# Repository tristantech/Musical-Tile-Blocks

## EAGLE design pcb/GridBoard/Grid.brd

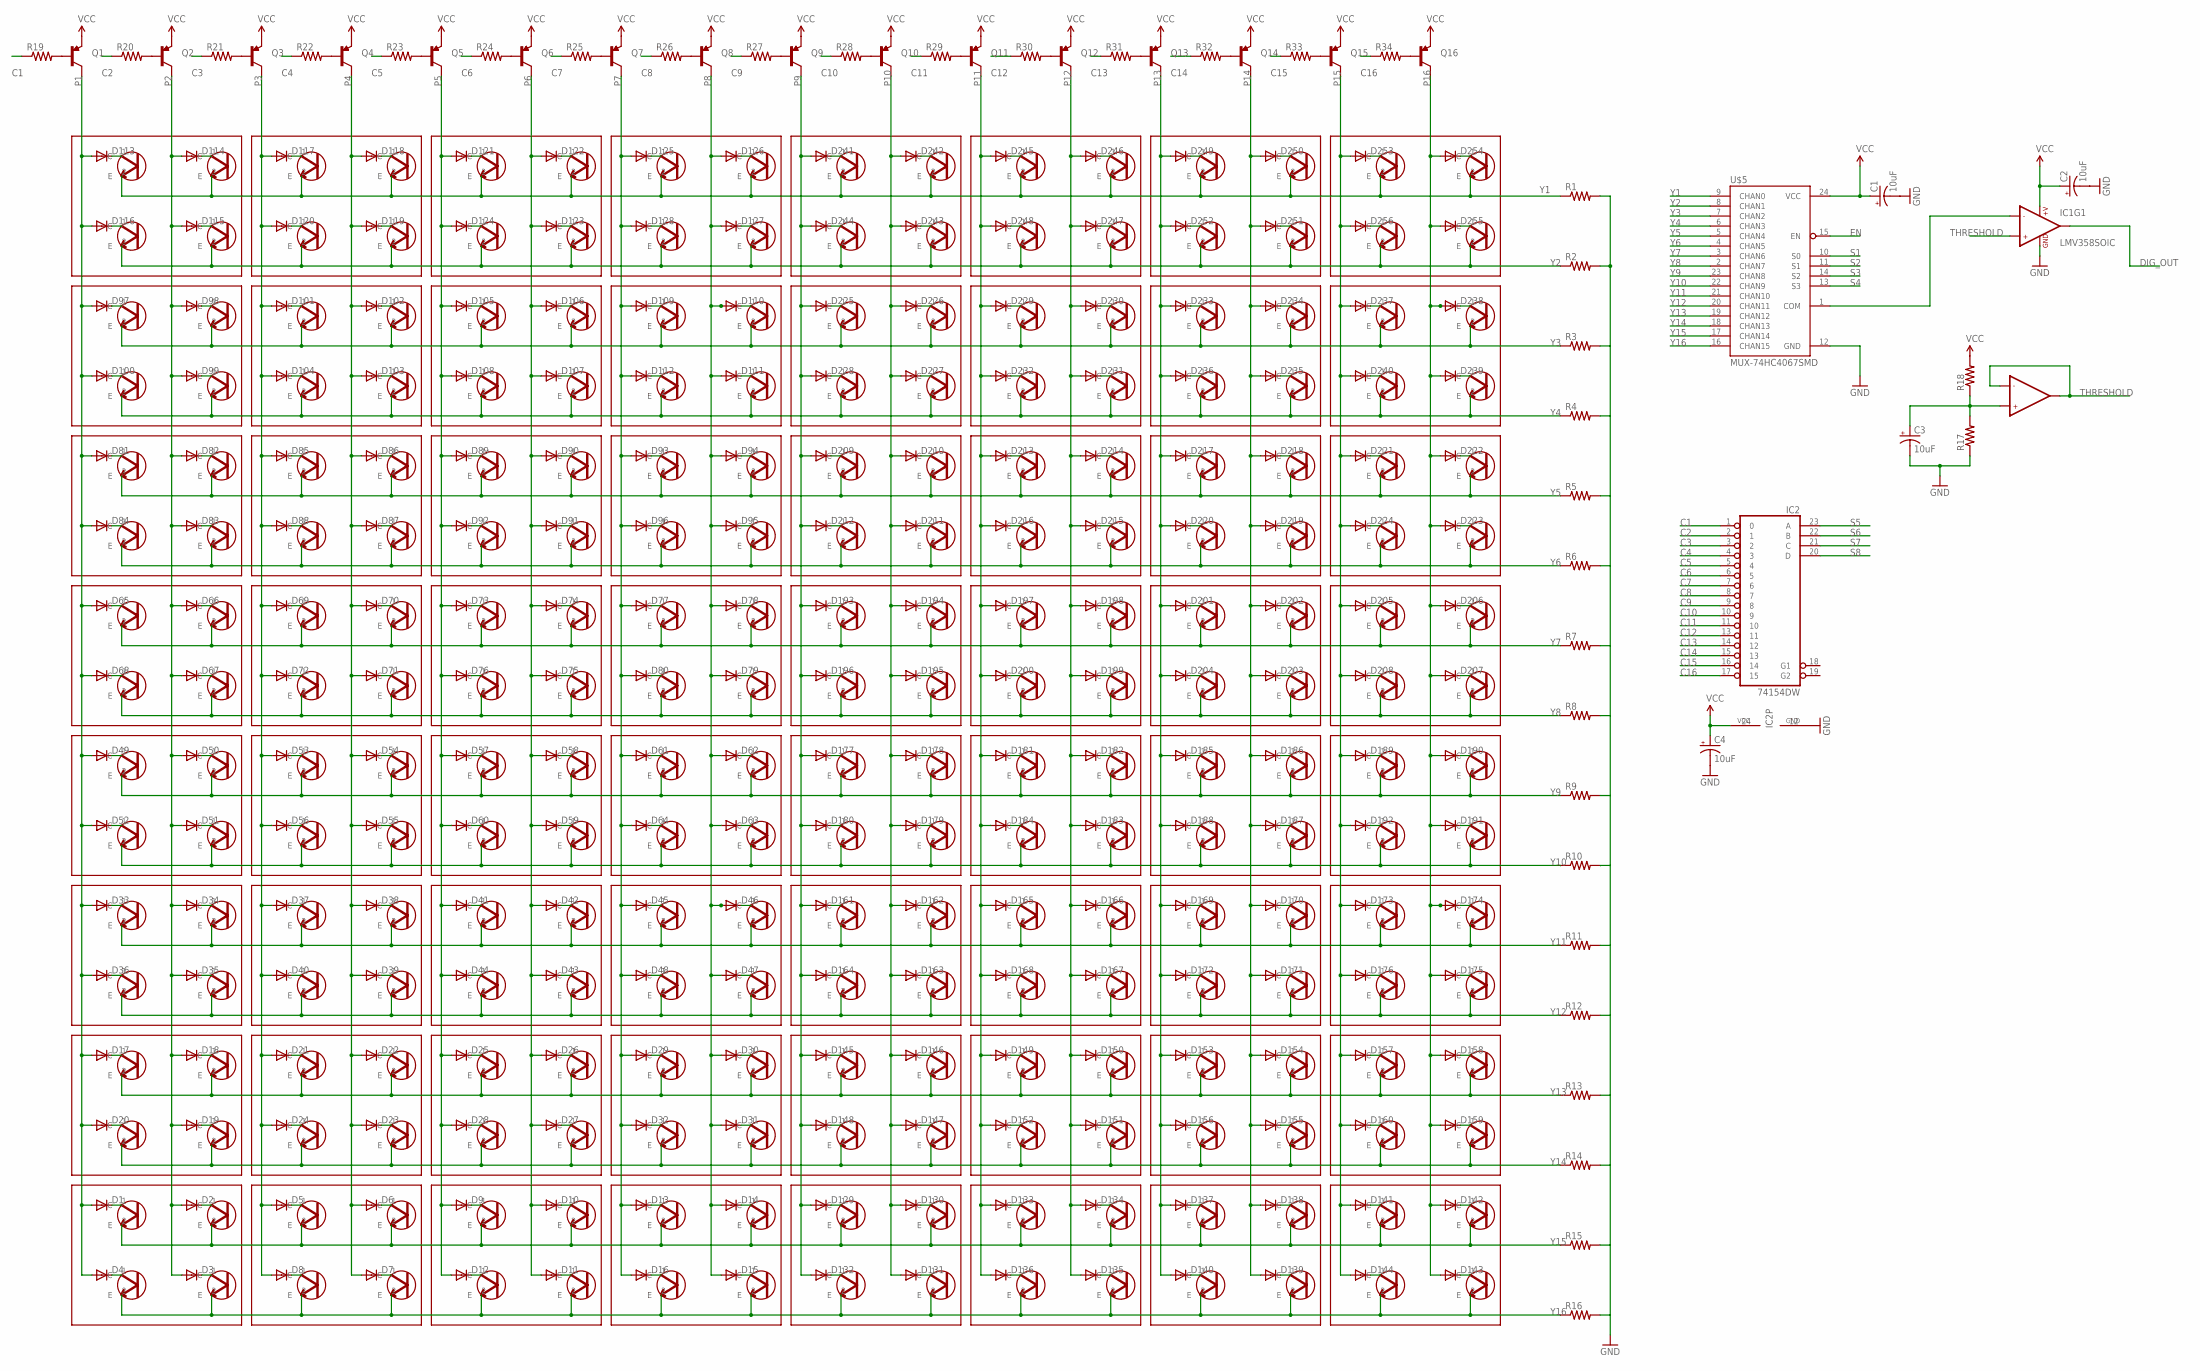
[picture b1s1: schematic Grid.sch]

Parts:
C1, C2, C3, C4: 10uF; EIA3216
D1, D2, D3, D4, D5, D6, D7, D8, D9, D10, D11, D12, D13, D14, D15, D16, D17, D18, D19, D20, D21, D22, D23, D24, D25, D26, D27, D28, D29, D30, D31, D32, D33, D34, D35, D36, D37, D38, D39, D40, D41, D42, D43, D44, D45, D46, D47, D48, D49, D50, D51, D52, D53, D54, D55, D56, D57, D58, D59, D60, D61, D62, D63, D64, D65, D66, D67, D68, D69, D70, D71, D72, D73, D74, D75, D76, D77, D78, D79, D80, D81, D82, D83, D84, D85, D86, D87, D88, D89, D90, D91, D92, D93, D94, D95, D96, D97, D98, D99, D100, D101, D102, D103, D104, D105, D106, D107, D108, D109, D110, D111, D112, D113, D114, D115, D116, D117, D118, D119, D120, D121, D122, D123, D124, D125, D126, D127, D128, D129, D130, D131, D132, D133, D134, D135, D136, D137, D138, D139, D140, D141, D142, D143, D144, D145, D146, D147, D148, D149, D150, D151, D152, D153, D154, D155, D156, D157, D158, D159, D160, D161, D162, D163, D164, D165, D166, D167, D168, D169, D170, D171, D172, D173, D174, D175, D176, D177, D178, D179, D180, D181, D182, D183, D184, D185, D186, D187, D188, D189, D190, D191, D192, D193, D194, D195, D196, D197, D198, D199, D200, D201, D202, D203, D204, D205, D206, D207, D208, D209, D210, D211, D212, D213, D214, D215, D216, D217, D218, D219, D220, D221, D222, D223, D224, D225, D226, D227, D228, D229, D230, D231, D232, D233, D234, D235, D236, D237, D238, D239, D240, D241, D242, D243, D244, D245, D246, D247, D248, D249, D250, D251, D252, D253, D254, D255, D256: DIODESOD; SOD-323
IC1: LMV358SOIC; SO08
IC2: 74154DW; SO24W
Q1, Q2, Q3, Q4, Q5, Q6, Q7, Q8, Q9, Q10, Q11, Q12, Q13, Q14, Q15, Q16: TRANSISTOR_PNPSMD; SOT23-3
R1, R2, R3, R4, R5, R6, R7, R8, R9, R10, R11, R12, R13, R14, R15, R16, R17, R18, R19, R20, R21, R22, R23, R24, R25, R26, R27, R28, R29, R30, R31, R32, R33, R34: RESISTOR0603; 0603-RES
U$1, U$2, U$3, U$4, U$6, U$7, U$8, U$9, U$10, U$11, U$12, U$13, U$14, U$15, U$16, U$17, U$18, U$19, U$20, U$21, U$22, U$23, U$24, U$25, U$26, U$27, U$28, U$29, U$30, U$31, U$32, U$33, U$34, U$35, U$36, U$37, U$38, U$39, U$40, U$41, U$42, U$43, U$44, U$45, U$46, U$47, U$48, U$49, U$50, U$51, U$52, U$53, U$54, U$55, U$56, U$57, U$58, U$59, U$60, U$61, U$62, U$63, U$64, U$65, U$66, U$67, U$68, U$69, U$70, U$71, U$72, U$73, U$74, U$75, U$76, U$77, U$78, U$79, U$80, U$81, U$82, U$83, U$84, U$85, U$86, U$87, U$88, U$89, U$90, U$91, U$92, U$93, U$94, U$95, U$96, U$97, U$98, U$99, U$100, U$101, U$102, U$103, U$104, U$105, U$106, U$107, U$108, U$109, U$110, U$111, U$112, U$113, U$114, U$115, U$116, U$117, U$118, U$119, U$120, U$121, U$122, U$123, U$124, U$125, U$126, U$127, U$128, U$129, U$130, U$131, U$132, U$133, U$134, U$135, U$136, U$137, U$138, U$139, U$140, U$141, U$142, U$143, U$144, U$145, U$146, U$147, U$148, U$149, U$150, U$151, U$152, U$153, U$154, U$155, U$156, U$157, U$158, U$159, U$160, U$161, U$162, U$163, U$164, U$165, U$166, U$167, U$168, U$169, U$170, U$171, U$172, U$173, U$174, U$175, U$176, U$177, U$178, U$179, U$180, U$181, U$182, U$183, U$184, U$185, U$186, U$187, U$188, U$189, U$190, U$191, U$192, U$193, U$194, U$195, U$196, U$197, U$198, U$199, U$200, U$201, U$202, U$203, U$204, U$205, U$206, U$207, U$208, U$209, U$210, U$211, U$212, U$213, U$214, U$215, U$216, U$217, U$218, U$219, U$220, U$221, U$222, U$223, U$224, U$225, U$226, U$227, U$228, U$229, U$230, U$231, U$232, U$233, U$234, U$235, U$236, U$237, U$238, U$239, U$240, U$241, U$242, U$243, U$244, U$245, U$246, U$247, U$248, U$249, U$250, U$251, U$252, U$253, U$254, U$255, U$256, U$257: PT15-21B; 1206
U$5: MUX-74HC4067SMD; SSOP24

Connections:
C1: IC2.1 (0), R19.1
C2: IC2.2 (1), R20.1
C3: IC2.3 (2), R21.1
C4: IC2.4 (3), R22.1
C5: IC2.5 (4), R23.1
C6: IC2.6 (5), R24.1
C7: IC2.7 (6), R25.1
C8: IC2.8 (7), R26.1
C9: IC2.9 (8), R27.1
C10: IC2.10 (9), R28.1
C11: IC2.11 (10), R29.1
C12: IC2.13 (11), R30.1
C13: IC2.14 (12), R31.1
C14: IC2.15 (13), R32.1
C15: IC2.16 (14), R33.1
C16: IC2.17 (15), R34.1
DIG_OUT: IC1.1 (OUT1)
EN: U$5.15 (EN)
GND: C1.C (-), C2.C (-), C3.C (-), C4.C (-), IC1.4 (GND), IC2.12 (GND), R1.2, R2.2, R3.2, R4.2, R5.2, R6.2, R7.2, R8.2, R9.2, R10.2, R11.2, R12.2, R13.2, R14.2, R15.2, R16.2, R17.1, U$5.12 (GND)
unnamed: Q1.1 (B), R19.2
unnamed: Q2.1 (B), R20.2
unnamed: IC1.2 (-IN1), U$5.1 (COM)
unnamed: D2.1 (C), U$2.1 (C)
unnamed: C3.A (+), IC1.5 (+IN2), R17.2, R18.1
unnamed: D1.1 (C), U$1.1 (C)
unnamed: D4.1 (C), U$4.1 (C)
unnamed: D3.1 (C), U$3.1 (C)
unnamed: Q3.1 (B), R21.2
unnamed: Q4.1 (B), R22.2
unnamed: Q5.1 (B), R23.2
unnamed: Q6.1 (B), R24.2
unnamed: D5.1 (C), U$6.1 (C)
unnamed: D6.1 (C), U$7.1 (C)
unnamed: D8.1 (C), U$9.1 (C)
unnamed: D7.1 (C), U$8.1 (C)
unnamed: Q7.1 (B), R25.2
unnamed: Q8.1 (B), R26.2
unnamed: Q9.1 (B), R27.2
unnamed: Q10.1 (B), R28.2
unnamed: D9.1 (C), U$10.1 (C)
unnamed: D10.1 (C), U$11.1 (C)
unnamed: D12.1 (C), U$13.1 (C)
unnamed: D11.1 (C), U$12.1 (C)
unnamed: Q11.1 (B), R29.2
unnamed: Q12.1 (B), R30.2
unnamed: Q13.1 (B), R31.2
unnamed: Q14.1 (B), R32.2
unnamed: D13.1 (C), U$14.1 (C)
unnamed: D14.1 (C), U$15.1 (C)
unnamed: D16.1 (C), U$17.1 (C)
unnamed: D15.1 (C), U$16.1 (C)
unnamed: Q15.1 (B), R33.2
unnamed: Q16.1 (B), R34.2
unnamed: D17.1 (C), U$18.1 (C)
unnamed: D18.1 (C), U$19.1 (C)
unnamed: D20.1 (C), U$21.1 (C)
unnamed: D19.1 (C), U$20.1 (C)
unnamed: D21.1 (C), U$22.1 (C)
unnamed: D22.1 (C), U$23.1 (C)
unnamed: D24.1 (C), U$25.1 (C)
unnamed: D23.1 (C), U$24.1 (C)
unnamed: D25.1 (C), U$26.1 (C)
unnamed: D26.1 (C), U$27.1 (C)
unnamed: D28.1 (C), U$29.1 (C)
unnamed: D27.1 (C), U$28.1 (C)
unnamed: D29.1 (C), U$30.1 (C)
unnamed: D30.1 (C), U$31.1 (C)
unnamed: D32.1 (C), U$33.1 (C)
unnamed: D31.1 (C), U$32.1 (C)
unnamed: D33.1 (C), U$34.1 (C)
unnamed: D34.1 (C), U$35.1 (C)
unnamed: D36.1 (C), U$37.1 (C)
unnamed: D35.1 (C), U$36.1 (C)
unnamed: D37.1 (C), U$38.1 (C)
unnamed: D38.1 (C), U$39.1 (C)
unnamed: D40.1 (C), U$41.1 (C)
unnamed: D39.1 (C), U$40.1 (C)
unnamed: D41.1 (C), U$42.1 (C)
unnamed: D42.1 (C), U$43.1 (C)
unnamed: D44.1 (C), U$45.1 (C)
unnamed: D43.1 (C), U$44.1 (C)
unnamed: D45.1 (C), U$46.1 (C)
unnamed: D46.1 (C), U$47.1 (C)
unnamed: D48.1 (C), U$49.1 (C)
unnamed: D47.1 (C), U$48.1 (C)
unnamed: D49.1 (C), U$50.1 (C)
unnamed: D50.1 (C), U$51.1 (C)
unnamed: D52.1 (C), U$53.1 (C)
unnamed: D51.1 (C), U$52.1 (C)
unnamed: D53.1 (C), U$54.1 (C)
unnamed: D54.1 (C), U$55.1 (C)
unnamed: D56.1 (C), U$57.1 (C)
unnamed: D55.1 (C), U$56.1 (C)
unnamed: D57.1 (C), U$58.1 (C)
unnamed: D58.1 (C), U$59.1 (C)
unnamed: D60.1 (C), U$61.1 (C)
unnamed: D59.1 (C), U$60.1 (C)
unnamed: D61.1 (C), U$62.1 (C)
unnamed: D62.1 (C), U$63.1 (C)
unnamed: D64.1 (C), U$65.1 (C)
unnamed: D63.1 (C), U$64.1 (C)
unnamed: D65.1 (C), U$66.1 (C)
unnamed: D66.1 (C), U$67.1 (C)
unnamed: D68.1 (C), U$69.1 (C)
unnamed: D67.1 (C), U$68.1 (C)
unnamed: D69.1 (C), U$70.1 (C)
unnamed: D70.1 (C), U$71.1 (C)
unnamed: D72.1 (C), U$73.1 (C)
unnamed: D71.1 (C), U$72.1 (C)
unnamed: D73.1 (C), U$74.1 (C)
unnamed: D74.1 (C), U$75.1 (C)
unnamed: D76.1 (C), U$77.1 (C)
unnamed: D75.1 (C), U$76.1 (C)
unnamed: D77.1 (C), U$78.1 (C)
unnamed: D78.1 (C), U$79.1 (C)
unnamed: D80.1 (C), U$81.1 (C)
unnamed: D79.1 (C), U$80.1 (C)
unnamed: D81.1 (C), U$82.1 (C)
unnamed: D82.1 (C), U$83.1 (C)
unnamed: D84.1 (C), U$85.1 (C)
unnamed: D83.1 (C), U$84.1 (C)
unnamed: D85.1 (C), U$86.1 (C)
unnamed: D86.1 (C), U$87.1 (C)
unnamed: D88.1 (C), U$89.1 (C)
unnamed: D87.1 (C), U$88.1 (C)
unnamed: D89.1 (C), U$90.1 (C)
unnamed: D90.1 (C), U$91.1 (C)
unnamed: D92.1 (C), U$93.1 (C)
unnamed: D91.1 (C), U$92.1 (C)
unnamed: D93.1 (C), U$94.1 (C)
unnamed: D94.1 (C), U$95.1 (C)
unnamed: D96.1 (C), U$97.1 (C)
unnamed: D95.1 (C), U$96.1 (C)
unnamed: D97.1 (C), U$98.1 (C)
unnamed: D98.1 (C), U$99.1 (C)
unnamed: D100.1 (C), U$101.1 (C)
unnamed: D99.1 (C), U$100.1 (C)
unnamed: D101.1 (C), U$102.1 (C)
unnamed: D102.1 (C), U$103.1 (C)
unnamed: D104.1 (C), U$105.1 (C)
unnamed: D103.1 (C), U$104.1 (C)
unnamed: D105.1 (C), U$106.1 (C)
unnamed: D106.1 (C), U$107.1 (C)
unnamed: D108.1 (C), U$109.1 (C)
unnamed: D107.1 (C), U$108.1 (C)
unnamed: D109.1 (C), U$110.1 (C)
unnamed: D110.1 (C), U$111.1 (C)
unnamed: D112.1 (C), U$113.1 (C)
unnamed: D111.1 (C), U$112.1 (C)
unnamed: D113.1 (C), U$114.1 (C)
unnamed: D114.1 (C), U$115.1 (C)
unnamed: D116.1 (C), U$117.1 (C)
unnamed: D115.1 (C), U$116.1 (C)
unnamed: D117.1 (C), U$118.1 (C)
unnamed: D118.1 (C), U$119.1 (C)
unnamed: D120.1 (C), U$121.1 (C)
unnamed: D119.1 (C), U$120.1 (C)
unnamed: D121.1 (C), U$122.1 (C)
unnamed: D122.1 (C), U$123.1 (C)
unnamed: D124.1 (C), U$125.1 (C)
unnamed: D123.1 (C), U$124.1 (C)
unnamed: D125.1 (C), U$126.1 (C)
unnamed: D126.1 (C), U$127.1 (C)
unnamed: D128.1 (C), U$129.1 (C)
unnamed: D127.1 (C), U$128.1 (C)
unnamed: D129.1 (C), U$130.1 (C)
unnamed: D130.1 (C), U$131.1 (C)
unnamed: D132.1 (C), U$133.1 (C)
unnamed: D131.1 (C), U$132.1 (C)
unnamed: D133.1 (C), U$134.1 (C)
unnamed: D134.1 (C), U$135.1 (C)
unnamed: D136.1 (C), U$137.1 (C)
unnamed: D135.1 (C), U$136.1 (C)
unnamed: D137.1 (C), U$138.1 (C)
unnamed: D138.1 (C), U$139.1 (C)
unnamed: D140.1 (C), U$141.1 (C)
unnamed: D139.1 (C), U$140.1 (C)
unnamed: D141.1 (C), U$142.1 (C)
unnamed: D142.1 (C), U$143.1 (C)
unnamed: D144.1 (C), U$145.1 (C)
unnamed: D143.1 (C), U$144.1 (C)
unnamed: D145.1 (C), U$146.1 (C)
unnamed: D146.1 (C), U$147.1 (C)
unnamed: D148.1 (C), U$149.1 (C)
unnamed: D147.1 (C), U$148.1 (C)
unnamed: D149.1 (C), U$150.1 (C)
unnamed: D150.1 (C), U$151.1 (C)
unnamed: D152.1 (C), U$153.1 (C)
unnamed: D151.1 (C), U$152.1 (C)
unnamed: D153.1 (C), U$154.1 (C)
unnamed: D154.1 (C), U$155.1 (C)
unnamed: D156.1 (C), U$157.1 (C)
unnamed: D155.1 (C), U$156.1 (C)
unnamed: D157.1 (C), U$158.1 (C)
unnamed: D158.1 (C), U$159.1 (C)
unnamed: D160.1 (C), U$161.1 (C)
unnamed: D159.1 (C), U$160.1 (C)
unnamed: D161.1 (C), U$162.1 (C)
unnamed: D162.1 (C), U$163.1 (C)
unnamed: D164.1 (C), U$165.1 (C)
unnamed: D163.1 (C), U$164.1 (C)
unnamed: D165.1 (C), U$166.1 (C)
unnamed: D166.1 (C), U$167.1 (C)
unnamed: D168.1 (C), U$169.1 (C)
unnamed: D167.1 (C), U$168.1 (C)
unnamed: D169.1 (C), U$170.1 (C)
unnamed: D170.1 (C), U$171.1 (C)
unnamed: D172.1 (C), U$173.1 (C)
unnamed: D171.1 (C), U$172.1 (C)
unnamed: D173.1 (C), U$174.1 (C)
unnamed: D174.1 (C), U$175.1 (C)
unnamed: D176.1 (C), U$177.1 (C)
unnamed: D175.1 (C), U$176.1 (C)
unnamed: D177.1 (C), U$178.1 (C)
unnamed: D178.1 (C), U$179.1 (C)
unnamed: D180.1 (C), U$181.1 (C)
unnamed: D179.1 (C), U$180.1 (C)
unnamed: D181.1 (C), U$182.1 (C)
unnamed: D182.1 (C), U$183.1 (C)
unnamed: D184.1 (C), U$185.1 (C)
unnamed: D183.1 (C), U$184.1 (C)
unnamed: D185.1 (C), U$186.1 (C)
unnamed: D186.1 (C), U$187.1 (C)
unnamed: D188.1 (C), U$189.1 (C)
unnamed: D187.1 (C), U$188.1 (C)
unnamed: D189.1 (C), U$190.1 (C)
unnamed: D190.1 (C), U$191.1 (C)
unnamed: D192.1 (C), U$193.1 (C)
unnamed: D191.1 (C), U$192.1 (C)
unnamed: D193.1 (C), U$194.1 (C)
unnamed: D194.1 (C), U$195.1 (C)
unnamed: D196.1 (C), U$197.1 (C)
unnamed: D195.1 (C), U$196.1 (C)
unnamed: D197.1 (C), U$198.1 (C)
unnamed: D198.1 (C), U$199.1 (C)
unnamed: D200.1 (C), U$201.1 (C)
unnamed: D199.1 (C), U$200.1 (C)
unnamed: D201.1 (C), U$202.1 (C)
unnamed: D202.1 (C), U$203.1 (C)
unnamed: D204.1 (C), U$205.1 (C)
unnamed: D203.1 (C), U$204.1 (C)
unnamed: D205.1 (C), U$206.1 (C)
unnamed: D206.1 (C), U$207.1 (C)
unnamed: D208.1 (C), U$209.1 (C)
unnamed: D207.1 (C), U$208.1 (C)
unnamed: D209.1 (C), U$210.1 (C)
unnamed: D210.1 (C), U$211.1 (C)
unnamed: D212.1 (C), U$213.1 (C)
unnamed: D211.1 (C), U$212.1 (C)
unnamed: D213.1 (C), U$214.1 (C)
unnamed: D214.1 (C), U$215.1 (C)
unnamed: D216.1 (C), U$217.1 (C)
unnamed: D215.1 (C), U$216.1 (C)
unnamed: D217.1 (C), U$218.1 (C)
unnamed: D218.1 (C), U$219.1 (C)
unnamed: D220.1 (C), U$221.1 (C)
unnamed: D219.1 (C), U$220.1 (C)
unnamed: D221.1 (C), U$222.1 (C)
unnamed: D222.1 (C), U$223.1 (C)
unnamed: D224.1 (C), U$225.1 (C)
unnamed: D223.1 (C), U$224.1 (C)
unnamed: D225.1 (C), U$226.1 (C)
unnamed: D226.1 (C), U$227.1 (C)
unnamed: D228.1 (C), U$229.1 (C)
unnamed: D227.1 (C), U$228.1 (C)
unnamed: D229.1 (C), U$230.1 (C)
unnamed: D230.1 (C), U$231.1 (C)
unnamed: D232.1 (C), U$233.1 (C)
unnamed: D231.1 (C), U$232.1 (C)
unnamed: D233.1 (C), U$234.1 (C)
unnamed: D234.1 (C), U$235.1 (C)
unnamed: D236.1 (C), U$237.1 (C)
unnamed: D235.1 (C), U$236.1 (C)
unnamed: D237.1 (C), U$238.1 (C)
unnamed: D238.1 (C), U$239.1 (C)
unnamed: D240.1 (C), U$241.1 (C)
unnamed: D239.1 (C), U$240.1 (C)
unnamed: D241.1 (C), U$242.1 (C)
unnamed: D242.1 (C), U$243.1 (C)
unnamed: D244.1 (C), U$245.1 (C)
unnamed: D243.1 (C), U$244.1 (C)
unnamed: D245.1 (C), U$246.1 (C)
unnamed: D246.1 (C), U$247.1 (C)
unnamed: D248.1 (C), U$249.1 (C)
unnamed: D247.1 (C), U$248.1 (C)
unnamed: D249.1 (C), U$250.1 (C)
unnamed: D250.1 (C), U$251.1 (C)
unnamed: D252.1 (C), U$253.1 (C)
unnamed: D251.1 (C), U$252.1 (C)
unnamed: D253.1 (C), U$254.1 (C)
unnamed: D254.1 (C), U$255.1 (C)
unnamed: D256.1 (C), U$257.1 (C)
unnamed: D255.1 (C), U$256.1 (C)
P1: D1.2 (A), D4.2 (A), D17.2 (A), D20.2 (A), D33.2 (A), D36.2 (A), D49.2 (A), D52.2 (A), D65.2 (A), D68.2 (A), D81.2 (A), D84.2 (A), D97.2 (A), D100.2 (A), D113.2 (A), D116.2 (A), Q1.3 (C)
P2: D2.2 (A), D3.2 (A), D18.2 (A), D19.2 (A), D34.2 (A), D35.2 (A), D50.2 (A), D51.2 (A), D66.2 (A), D67.2 (A), D82.2 (A), D83.2 (A), D98.2 (A), D99.2 (A), D114.2 (A), D115.2 (A), Q2.3 (C)
P3: D5.2 (A), D8.2 (A), D21.2 (A), D24.2 (A), D37.2 (A), D40.2 (A), D53.2 (A), D56.2 (A), D69.2 (A), D72.2 (A), D85.2 (A), D88.2 (A), D101.2 (A), D104.2 (A), D117.2 (A), D120.2 (A), Q3.3 (C)
P4: D6.2 (A), D7.2 (A), D22.2 (A), D23.2 (A), D38.2 (A), D39.2 (A), D54.2 (A), D55.2 (A), D70.2 (A), D71.2 (A), D86.2 (A), D87.2 (A), D102.2 (A), D103.2 (A), D118.2 (A), D119.2 (A), Q4.3 (C)
P5: D9.2 (A), D12.2 (A), D25.2 (A), D28.2 (A), D41.2 (A), D44.2 (A), D57.2 (A), D60.2 (A), D73.2 (A), D76.2 (A), D89.2 (A), D92.2 (A), D105.2 (A), D108.2 (A), D121.2 (A), D124.2 (A), Q5.3 (C)
P6: D10.2 (A), D11.2 (A), D26.2 (A), D27.2 (A), D42.2 (A), D43.2 (A), D58.2 (A), D59.2 (A), D74.2 (A), D75.2 (A), D90.2 (A), D91.2 (A), D106.2 (A), D107.2 (A), D122.2 (A), D123.2 (A), Q6.3 (C)
P7: D13.2 (A), D16.2 (A), D29.2 (A), D32.2 (A), D45.2 (A), D48.2 (A), D61.2 (A), D64.2 (A), D77.2 (A), D80.2 (A), D93.2 (A), D96.2 (A), D109.2 (A), D112.2 (A), D125.2 (A), D128.2 (A), Q7.3 (C)
P8: D14.2 (A), D15.2 (A), D30.2 (A), D31.2 (A), D46.2 (A), D47.2 (A), D62.2 (A), D63.2 (A), D78.2 (A), D79.2 (A), D94.2 (A), D95.2 (A), D110.2 (A), D111.2 (A), D126.2 (A), D127.2 (A), Q8.3 (C)
P9: D129.2 (A), D132.2 (A), D145.2 (A), D148.2 (A), D161.2 (A), D164.2 (A), D177.2 (A), D180.2 (A), D193.2 (A), D196.2 (A), D209.2 (A), D212.2 (A), D225.2 (A), D228.2 (A), D241.2 (A), D244.2 (A), Q9.3 (C)
P10: D130.2 (A), D131.2 (A), D146.2 (A), D147.2 (A), D162.2 (A), D163.2 (A), D178.2 (A), D179.2 (A), D194.2 (A), D195.2 (A), D210.2 (A), D211.2 (A), D226.2 (A), D227.2 (A), D242.2 (A), D243.2 (A), Q10.3 (C)
P11: D133.2 (A), D136.2 (A), D149.2 (A), D152.2 (A), D165.2 (A), D168.2 (A), D181.2 (A), D184.2 (A), D197.2 (A), D200.2 (A), D213.2 (A), D216.2 (A), D229.2 (A), D232.2 (A), D245.2 (A), D248.2 (A), Q11.3 (C)
P12: D134.2 (A), D135.2 (A), D150.2 (A), D151.2 (A), D166.2 (A), D167.2 (A), D182.2 (A), D183.2 (A), D198.2 (A), D199.2 (A), D214.2 (A), D215.2 (A), D230.2 (A), D231.2 (A), D246.2 (A), D247.2 (A), Q12.3 (C)
P13: D137.2 (A), D140.2 (A), D153.2 (A), D156.2 (A), D169.2 (A), D172.2 (A), D185.2 (A), D188.2 (A), D201.2 (A), D204.2 (A), D217.2 (A), D220.2 (A), D233.2 (A), D236.2 (A), D249.2 (A), D252.2 (A), Q13.3 (C)
P14: D138.2 (A), D139.2 (A), D154.2 (A), D155.2 (A), D170.2 (A), D171.2 (A), D186.2 (A), D187.2 (A), D202.2 (A), D203.2 (A), D218.2 (A), D219.2 (A), D234.2 (A), D235.2 (A), D250.2 (A), D251.2 (A), Q14.3 (C)
P15: D141.2 (A), D144.2 (A), D157.2 (A), D160.2 (A), D173.2 (A), D176.2 (A), D189.2 (A), D192.2 (A), D205.2 (A), D208.2 (A), D221.2 (A), D224.2 (A), D237.2 (A), D240.2 (A), D253.2 (A), D256.2 (A), Q15.3 (C)
P16: D142.2 (A), D143.2 (A), D158.2 (A), D159.2 (A), D174.2 (A), D175.2 (A), D190.2 (A), D191.2 (A), D206.2 (A), D207.2 (A), D222.2 (A), D223.2 (A), D238.2 (A), D239.2 (A), D254.2 (A), D255.2 (A), Q16.3 (C)
S1: U$5.10 (S0)
S2: U$5.11 (S1)
S3: U$5.14 (S2)
S4: U$5.13 (S3)
S5: IC2.23 (A)
S6: IC2.22 (B)
S7: IC2.21 (C)
S8: IC2.20 (D)
THRESHOLD: IC1.3 (+IN1), IC1.6 (-IN2), IC1.7 (OUT2)
VCC: C1.A (+), C2.A (+), C4.A (+), IC1.8 (+V), IC2.24 (VCC), Q1.2 (E), Q2.2 (E), Q3.2 (E), Q4.2 (E), Q5.2 (E), Q6.2 (E), Q7.2 (E), Q8.2 (E), Q9.2 (E), Q10.2 (E), Q11.2 (E), Q12.2 (E), Q13.2 (E), Q14.2 (E), Q15.2 (E), Q16.2 (E), R18.2, U$5.24 (VCC)
Y1: R1.1, U$5.9 (CHAN0), U$114.2 (E), U$115.2 (E), U$118.2 (E), U$119.2 (E), U$122.2 (E), U$123.2 (E), U$126.2 (E), U$127.2 (E), U$242.2 (E), U$243.2 (E), U$246.2 (E), U$247.2 (E), U$250.2 (E), U$251.2 (E), U$254.2 (E), U$255.2 (E)
Y2: R2.1, U$5.8 (CHAN1), U$116.2 (E), U$117.2 (E), U$120.2 (E), U$121.2 (E), U$124.2 (E), U$125.2 (E), U$128.2 (E), U$129.2 (E), U$244.2 (E), U$245.2 (E), U$248.2 (E), U$249.2 (E), U$252.2 (E), U$253.2 (E), U$256.2 (E), U$257.2 (E)
Y3: R3.1, U$5.7 (CHAN2), U$98.2 (E), U$99.2 (E), U$102.2 (E), U$103.2 (E), U$106.2 (E), U$107.2 (E), U$110.2 (E), U$111.2 (E), U$226.2 (E), U$227.2 (E), U$230.2 (E), U$231.2 (E), U$234.2 (E), U$235.2 (E), U$238.2 (E), U$239.2 (E)
Y4: R4.1, U$5.6 (CHAN3), U$100.2 (E), U$101.2 (E), U$104.2 (E), U$105.2 (E), U$108.2 (E), U$109.2 (E), U$112.2 (E), U$113.2 (E), U$228.2 (E), U$229.2 (E), U$232.2 (E), U$233.2 (E), U$236.2 (E), U$237.2 (E), U$240.2 (E), U$241.2 (E)
Y5: R5.1, U$5.5 (CHAN4), U$82.2 (E), U$83.2 (E), U$86.2 (E), U$87.2 (E), U$90.2 (E), U$91.2 (E), U$94.2 (E), U$95.2 (E), U$210.2 (E), U$211.2 (E), U$214.2 (E), U$215.2 (E), U$218.2 (E), U$219.2 (E), U$222.2 (E), U$223.2 (E)
Y6: R6.1, U$5.4 (CHAN5), U$84.2 (E), U$85.2 (E), U$88.2 (E), U$89.2 (E), U$92.2 (E), U$93.2 (E), U$96.2 (E), U$97.2 (E), U$212.2 (E), U$213.2 (E), U$216.2 (E), U$217.2 (E), U$220.2 (E), U$221.2 (E), U$224.2 (E), U$225.2 (E)
Y7: R7.1, U$5.3 (CHAN6), U$66.2 (E), U$67.2 (E), U$70.2 (E), U$71.2 (E), U$74.2 (E), U$75.2 (E), U$78.2 (E), U$79.2 (E), U$194.2 (E), U$195.2 (E), U$198.2 (E), U$199.2 (E), U$202.2 (E), U$203.2 (E), U$206.2 (E), U$207.2 (E)
Y8: R8.1, U$5.2 (CHAN7), U$68.2 (E), U$69.2 (E), U$72.2 (E), U$73.2 (E), U$76.2 (E), U$77.2 (E), U$80.2 (E), U$81.2 (E), U$196.2 (E), U$197.2 (E), U$200.2 (E), U$201.2 (E), U$204.2 (E), U$205.2 (E), U$208.2 (E), U$209.2 (E)
Y9: R9.1, U$5.23 (CHAN8), U$50.2 (E), U$51.2 (E), U$54.2 (E), U$55.2 (E), U$58.2 (E), U$59.2 (E), U$62.2 (E), U$63.2 (E), U$178.2 (E), U$179.2 (E), U$182.2 (E), U$183.2 (E), U$186.2 (E), U$187.2 (E), U$190.2 (E), U$191.2 (E)
Y10: R10.1, U$5.22 (CHAN9), U$52.2 (E), U$53.2 (E), U$56.2 (E), U$57.2 (E), U$60.2 (E), U$61.2 (E), U$64.2 (E), U$65.2 (E), U$180.2 (E), U$181.2 (E), U$184.2 (E), U$185.2 (E), U$188.2 (E), U$189.2 (E), U$192.2 (E), U$193.2 (E)
Y11: R11.1, U$5.21 (CHAN10), U$34.2 (E), U$35.2 (E), U$38.2 (E), U$39.2 (E), U$42.2 (E), U$43.2 (E), U$46.2 (E), U$47.2 (E), U$162.2 (E), U$163.2 (E), U$166.2 (E), U$167.2 (E), U$170.2 (E), U$171.2 (E), U$174.2 (E), U$175.2 (E)
Y12: R12.1, U$5.20 (CHAN11), U$36.2 (E), U$37.2 (E), U$40.2 (E), U$41.2 (E), U$44.2 (E), U$45.2 (E), U$48.2 (E), U$49.2 (E), U$164.2 (E), U$165.2 (E), U$168.2 (E), U$169.2 (E), U$172.2 (E), U$173.2 (E), U$176.2 (E), U$177.2 (E)
Y13: R13.1, U$5.19 (CHAN12), U$18.2 (E), U$19.2 (E), U$22.2 (E), U$23.2 (E), U$26.2 (E), U$27.2 (E), U$30.2 (E), U$31.2 (E), U$146.2 (E), U$147.2 (E), U$150.2 (E), U$151.2 (E), U$154.2 (E), U$155.2 (E), U$158.2 (E), U$159.2 (E)
Y14: R14.1, U$5.18 (CHAN13), U$20.2 (E), U$21.2 (E), U$24.2 (E), U$25.2 (E), U$28.2 (E), U$29.2 (E), U$32.2 (E), U$33.2 (E), U$148.2 (E), U$149.2 (E), U$152.2 (E), U$153.2 (E), U$156.2 (E), U$157.2 (E), U$160.2 (E), U$161.2 (E)
Y15: R15.1, U$1.2 (E), U$2.2 (E), U$5.17 (CHAN14), U$6.2 (E), U$7.2 (E), U$10.2 (E), U$11.2 (E), U$14.2 (E), U$15.2 (E), U$130.2 (E), U$131.2 (E), U$134.2 (E), U$135.2 (E), U$138.2 (E), U$139.2 (E), U$142.2 (E), U$143.2 (E)
Y16: R16.1, U$3.2 (E), U$4.2 (E), U$5.16 (CHAN15), U$8.2 (E), U$9.2 (E), U$12.2 (E), U$13.2 (E), U$16.2 (E), U$17.2 (E), U$132.2 (E), U$133.2 (E), U$136.2 (E), U$137.2 (E), U$140.2 (E), U$141.2 (E), U$144.2 (E), U$145.2 (E)

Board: 2 copper layers, 569 parts (0 on the bottom side), 325 nets, no tracks yet.

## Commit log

2014-11-05 Initial commit of the circuit board
2014-11-05 Large progress on schematic, and created blank board file. Comparator circuit requires review and components must be labeled

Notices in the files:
parts and their libraries:
1_SparkFun-DiscreteSemi: Licensing: CC v3.0 Share-Alike You are welcome to use this library for commercial purposes.
1_SparkFun-AnalogIC: Licensing:Creative Commons ShareAlike 4.0 International - https://creativecommons.org/licenses/by-sa/4.0
